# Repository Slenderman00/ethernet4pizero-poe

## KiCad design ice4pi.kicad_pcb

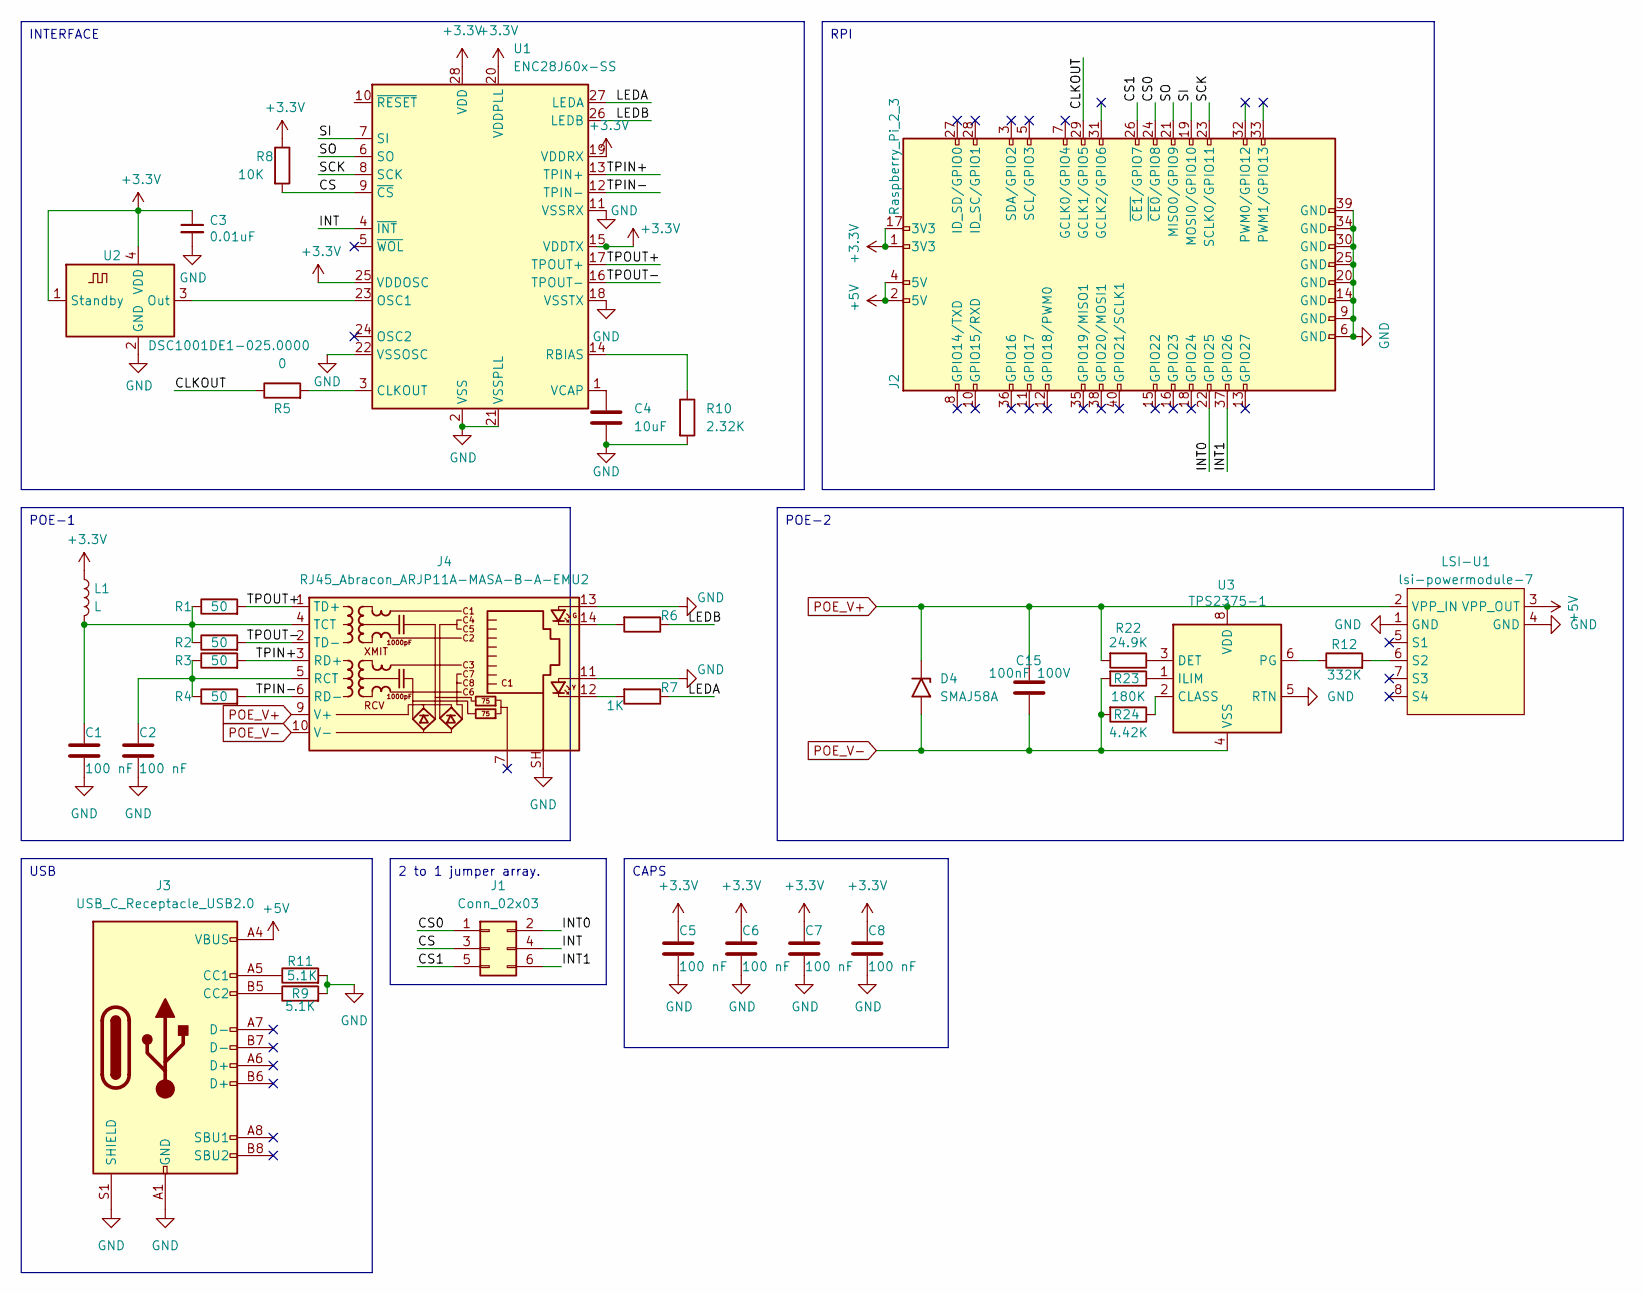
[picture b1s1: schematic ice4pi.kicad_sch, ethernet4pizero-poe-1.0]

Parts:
C1, C2, C5, C6, C7, C8: 100 nF; C_0402_1005Metric
C3: 0.01uF; C_0402_1005Metric
C4: 10uF; C_0402_1005Metric
C15: 100nF 100V; C_0402_1005Metric
D4: SMAJ58A; D_SMA
J1: Conn_02x03; PinHeader_2x03_P2.54mm_Vertical
J2: Raspberry_Pi_2_3; PinSocket_2x20_P2.54mm_Vertical_1_04mm
J3: USB_C_Receptacle_USB2.0; USB_C_Receptacle_GCT_USB4105-xx-A_16P_TopMnt_Horizontal
J4: RJ45_Abracon_ARJP11A-MASA-B-A-EMU2; RJ45_Abracon_ARJP11A-MA_Horizontal
L1: L; L_1210_3225Metric
LSI-U1: lsi-powermodule-7
R1, R2, R3, R4: 50; R_0402_1005Metric
R5: 0; R_0402_1005Metric
R6, R7: 1K; R_0402_1005Metric
R8: 10K; C_0402_1005Metric
R9, R11: 5.1K; R_0402_1005Metric
R10: 2.32K; R_0402_1005Metric
R12: 332K; R_0402_1005Metric
R22: 24.9K; R_0402_1005Metric
R23: 180K; R_0402_1005Metric
R24: 4.42K; R_0402_1005Metric
U1: ENC28J60x-SS; SSOP-28_5.3x10.2mm_P0.65mm
U2: DSC1001DE1-025.0000; Oscillator_SMD_Abracon_ASDMB-4Pin_2.5x2.0mm
U3: TPS2375-1; TSSOP-8_4.4x3mm_P0.65mm

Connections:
+3.3V: C3.1, C5.1, C6.1, C7.1, C8.1, J2.1 (3V3), J2.17 (3V3), L1.1, R8.1, U1.15 (VDDTX), U1.19 (VDDRX), U1.20 (VDDPLL), U1.25 (VDDOSC), U1.28 (VDD), U2.1 (Standby), U2.4 (VDD)
+5V: J2.2 (5V), J2.4 (5V), J3.A4 (VBUS), J3.A9 (VBUS), J3.B4 (VBUS), J3.B9 (VBUS), LSI-U1.3 (VPP_OUT)
/CLKOUT: J2.29 (GCLK1/GPIO5), R5.1
/CS: J1.3, R8.2, U1.9 (~CS)
/CS0: J1.1, J2.24 (~CE0/GPIO8)
/CS1: J1.5, J2.26 (~CE1/GPIO7)
/INT: J1.4, U1.4 (~INT)
/INT0: J1.2, J2.22 (GPIO25)
/INT1: J1.6, J2.37 (GPIO26)
/LEDA: R7.1, U1.27 (LEDA)
/LEDB: R6.1, U1.26 (LEDB)
/SCK: J2.23 (SCLK0/GPIO11), U1.8 (SCK)
/SI: J2.19 (MOSI0/GPIO10), U1.7 (SI)
/SO: J2.21 (MISO0/GPIO9), U1.6 (SO)
/TPIN+: J4.3 (RD+), R3.2, U1.13 (TPIN+)
/TPIN-: J4.6 (RD-), R4.2, U1.12 (TPIN-)
/TPOUT+: J4.1 (TD+), R1.2, U1.17 (TPOUT+)
/TPOUT-: J4.2 (TD-), R2.2, U1.16 (TPOUT-)
GND: C1.2, C2.2, C3.2, C4.2, C5.2, C6.2, C7.2, C8.2, J2.6 (GND), J2.9 (GND), J2.14 (GND), J2.20 (GND), J2.25 (GND), J2.30 (GND), J2.34 (GND), J2.39 (GND), J3.A1 (GND), J3.A12 (GND), J3.B1 (GND), J3.B12 (GND), J3.S1 (SHIELD), J4.11, J4.13, J4.SH, LSI-U1.1 (GND), LSI-U1.4 (GND), R9.2, R10.2, R11.2, U1.2 (VSS), U1.11 (VSSRX), U1.18 (VSSTX), U1.21 (VSSPLL), U1.22 (VSSOSC), U2.2 (GND), U3.5 (RTN)
unnamed: J3.A5 (CC1), R11.1
unnamed: J3.B5 (CC2), R9.1
unnamed: J4.12, R7.2
unnamed: J4.14, R6.2
unnamed: C2.1, J4.5 (RCT), R3.1, R4.1
unnamed: C1.1, J4.4 (TCT), L1.2, R1.1, R2.1
unnamed: LSI-U1.6 (S2), R12.2
unnamed: R5.2, U1.3 (CLKOUT)
unnamed: U1.23 (OSC1), U2.3 (Out)
unnamed: R10.1, U1.14 (RBIAS)
unnamed: C4.1, U1.1 (VCAP)
unnamed: R24.1, U3.2 (CLASS)
unnamed: R22.1, U3.3 (DET)
unnamed: R23.1, U3.1 (ILIM)
unnamed: R12.1, U3.6 (PG)
POE_V+: C15.1, D4.1 (A1), J4.9 (V+), LSI-U1.2 (VPP_IN), R22.2, U3.8 (VDD)
POE_V-: C15.2, D4.2 (A2), J4.10 (V-), R23.2, R24.2, U3.4 (VSS)

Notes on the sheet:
INTERFACE
RPI
POE-2
CAPS
POE-1
USB
2 to 1 jumper array.

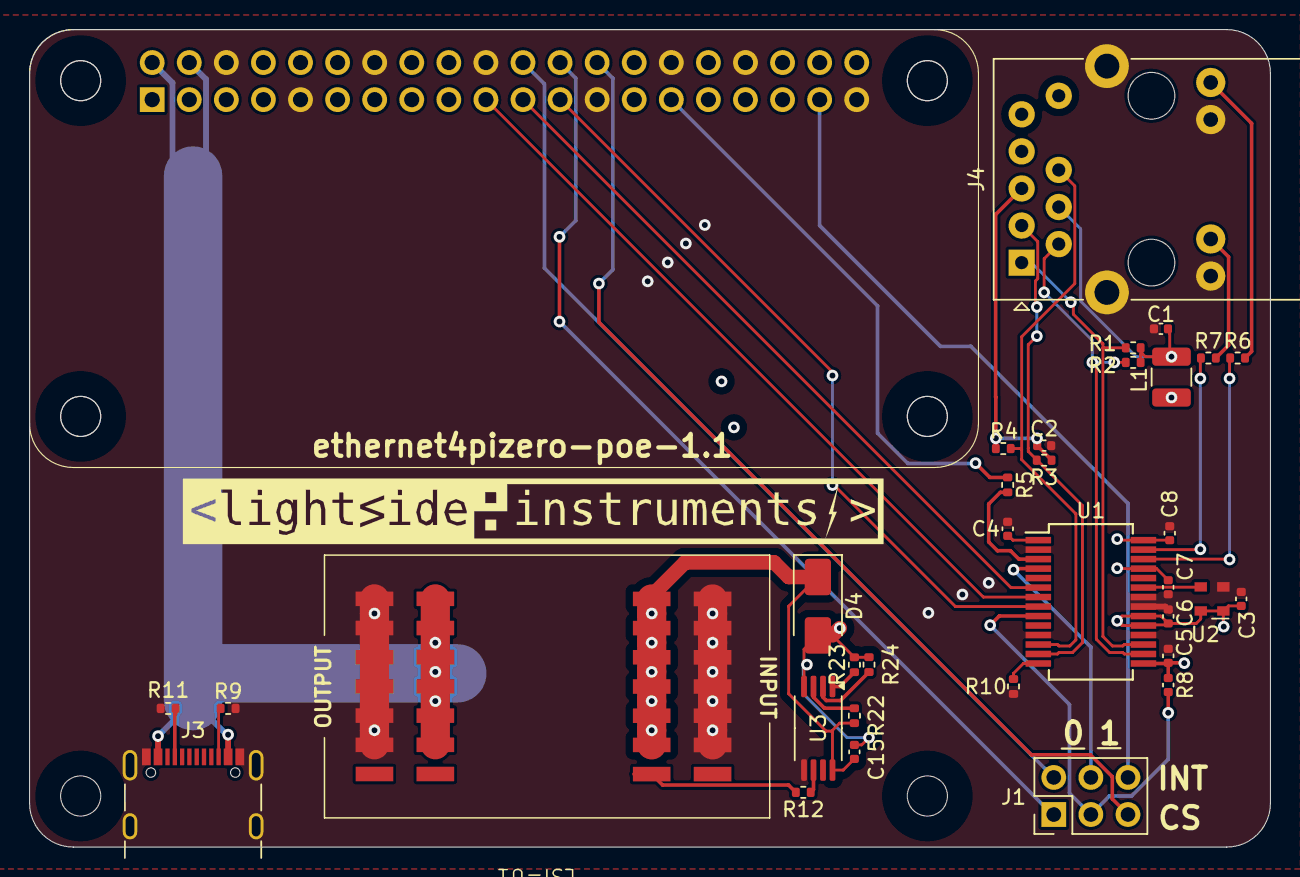
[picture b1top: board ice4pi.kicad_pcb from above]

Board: 4 copper layers, 85.0 x 56.0 mm, 35 parts (1 on the bottom side), 36 nets.

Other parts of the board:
svg2mod: G***; lsi-logo-48mm

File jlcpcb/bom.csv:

Comment,Designator,Footprint,JLCPCB Part #
ENC28J60x-SS,U1,Package_SO:SSOP-28_5.3x10.2mm_P0.65mm,C411626
10uF,C4,CAP-SMD_BD10.0-L10.3-W10.3-LS11.3-FD,C527590
50,"R1,R2,R3,R4",Resistor_SMD:R_0402_1005Metric,C149909
RJ45_Abracon_ARJP11A-MASA-B-A-EMU2,J4,Connector _RJ45_Abracon_ARJP11A-MASA-B-A-EMU2,C363363
0,R5,Resistor_SMD:R_0402_1005Metric,C176107
2.32K,R10,Resistor_SMD:R_0402_1005Metric,C334666
Conn_02x03,J1,Connector_PinHeader_2.54mm:PinHeader_2x03_P2.54mm_Vertical,C5116479
5.1K,"R9,R11",Resistor_SMD:R_0402_1005Metric,C105872
L,L1,Inductor_SMD:L_1210_3225Metric,C139159
1K,"R6,R7",Resistor_SMD:R_0402_1005Metric,C27998
100nF,"C1,C2,C5,C6,C7,C8",Capacitor_SMD:C_0402_1005Metric,C1525
USB_C_Receptacle_USB2.0,J3,Connector_USB:USB_C_Receptacle_GCT_USB4105-xx-A_16P_TopMnt_Horizontal,C167321
DSC1001DI1-025.0000,U2,Oscillator:Oscillator_SMD_Abracon_ASDMB-4Pin_2.5x2.0mm,C255956
10K,R8,Capacitor_SMD:C_0402_1005Metric,C25744
0.01uF,C3,Capacitor_SMD:C_0402_1005Metric,C15195
SMAJ58A,D4,SMAJ58A,
100nF 100v,C15,Capacitor_SMD:C_0402_1005Metric,
24.9K,R22,Resistor_SMD:R_0402_1005Metric,
180K,R23,Resistor_SMD:R_0402_1005Metric,
4.42K,R24,Resistor_SMD:R_0402_1005Metric,
TPS2375-1,U3,TPS2375-1,

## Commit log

2024-07-25 feat: poe
2024-07-25 feat: commit 2
2024-07-26 feat: poe controller
2024-07-26 feat: finished poe-1.0
2024-07-26 fix: added resistor
2024-07-26 feat: pos.csv
2024-08-01 fix: poe_v- trace width
2024-09-20 fix: fixed powermod footprint
2024-11-07 fix: no thermal reliefs
2024-11-07 fix: better paths
2024-11-07 fix: led
2024-11-11 feat: changed power traces layer
2024-11-11 fix: using correct powermod footprint
2024-11-11 fix: fixed led polarity
2024-11-11 fix: cosmetics
2024-11-25 todo: fix led polarity
2025-01-09 fix: powergood is an open drain
2025-01-09 feat: fixed led polarity
